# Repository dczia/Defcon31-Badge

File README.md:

# Defcon31-Badge
DCZia 2023 DC31 Badge - Electric Sampler

```
   ____  ___________   _          ________          __       _
   / __ \/ ____/__  /  (_)___ _   / ____/ /__  _____/ /______(_)____
  / / / / /      / /  / / __ `/  / __/ / / _ \/ ___/ __/ ___/ / ___/
 / /_/ / /___   / /__/ / /_/ /  / /___/ /  __/ /__/ /_/ /  / / /__
/_____/\____/  /____/_/\__,_/  /_____/_/\___/\___/\__/_/  /_/\___/

   _____                       __
  / ___/____ _____ ___  ____  / /__  _____
  \__ \/ __ `/ __ `__ \/ __ \/ / _ \/ ___/
 ___/ / /_/ / / / / / / /_/ / /  __/ /
/____/\__,_/_/ /_/ /_/ .___/_/\___/_/
                    /_/
```

## About
The DCZia Electric Sampler - A eurorack format drum machine, sampler, and step sequencer powered by
the Pi2040.

## Specs

RPI 2040 Microconroller
OLED Screen
3.5mm Audio Out Jack
3.5mm Midi In / Out (TRRS)
3.5mm Sync In / Out
MicroSD Card Slot
Eurorack Power Connector
Battery Power

## Build Guide

The badge comes with all surface mount components already assembled on the board. You will need to
solder on the keyswitches, audio jacks, screen, rotary encoders, and battery box.

First add the audio jacks. Install all the jacks and make sure they are flat and perpendicular with
the board. Next install the front board first aligning the jacks with the holes in the front board.
Then connect the bottom pin header to the front board. The header will be off by one, THIS IS OK for
the v1.1 board! Then carefully flip over the board and solder on the jacks.

Remove the front panel.

Then insert a keyswitch, or all keyswitches onto the board. Check that the metal pins are not bent,
and if so gently straignten them out with your fingers or a pair of tweezers. Carfully flip the
board over and solder on the keyswitches.

Next add the rotary encoders. Push them through the board, and you may need to gently fold in the
side stabilization pins if they do not line up correctly. Flip over the board and solder these in. 

Next with the board facing forward and on a flat surface, put the screen in. The legs of the screen
should not protrude through the back of the board past the holes, or only a tiny bit. You may need
to use something like a pencil or something to help the screen lay flat, standing off from the
board. Gently solder from the front to establish a mechanical connection to the board, then once the
screen is secure, flip over and solder the back. You must solder the back pads to endure a
connection from the screen to the microcrontroller. 

Finally flip the board over and gently attach the battery pack somewhere on the back with the
supplied double sticky tape. Then solder on the leads from the battery pack to the pads on the
bottom left side of the back of the board.

## User Manual

Currently the firmware is not complete, and the user interface may change.

The Select Knob will change between options on the screen, and push selects the currently
highlighted option.

The Volume knob will change the volume.

The PLAY button will play / pause any currently running program

There are a few modes on the v1 software.
A LED light mode.
A Sampler mode with a sequencer. You can load a wav file from the onboard flash, and then add a sequence and control the steps with the 8 key switches, and adjust per step volume.
A Sequencer mode which will play pre progarmed sequences. (Still under dev)
A Midi controller mode. You can adjust what notes / cc params are output via the python code in our repo.
A USB HID Device mode. The keys will output 0-9 and the device will emulate a keyboard.

## Notes

If you picked up a V1 board at Con, the board shipped with our testing firmware. Please flash the V1 firmware for more features.

Additional Features and changes will be coming soon!

## Updating the software / firmware

To update the software on the board you can do two things.

1. Use the fimware blob from our release section. To use this, unplug and turn off the module. Using something non conductivem press and hold the button on the RPI 2040 (The BootSelect Button) while powering on the unit via a micro usb cable. You should then see a mass storage drive appear on your computer. Drag the single uf2 file onto the drive. Then the unit should restart with the new firmware.

2. You can also plug the unit into your computer via the micro usb and drag the contents of the Production/Software folder onto the mass storage drive. The unit should reboot when complete. Sometimes if your computer transfers the files too slow this can cause issues with the RPI rebooting before all the software is complete.

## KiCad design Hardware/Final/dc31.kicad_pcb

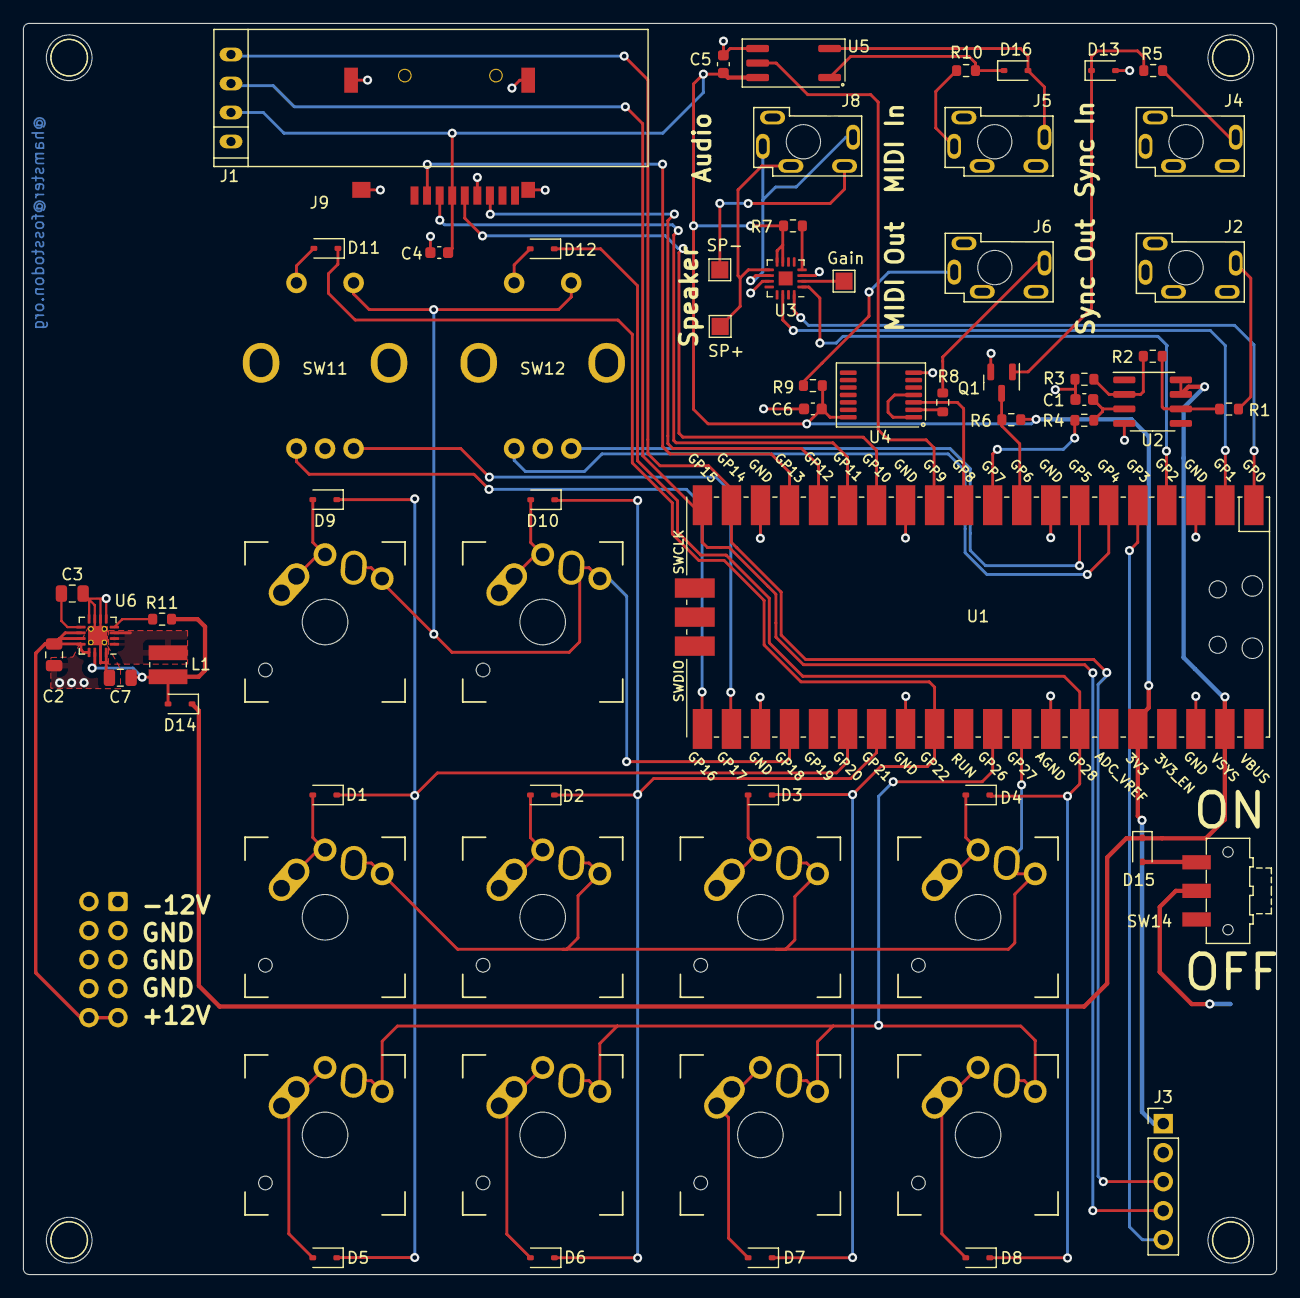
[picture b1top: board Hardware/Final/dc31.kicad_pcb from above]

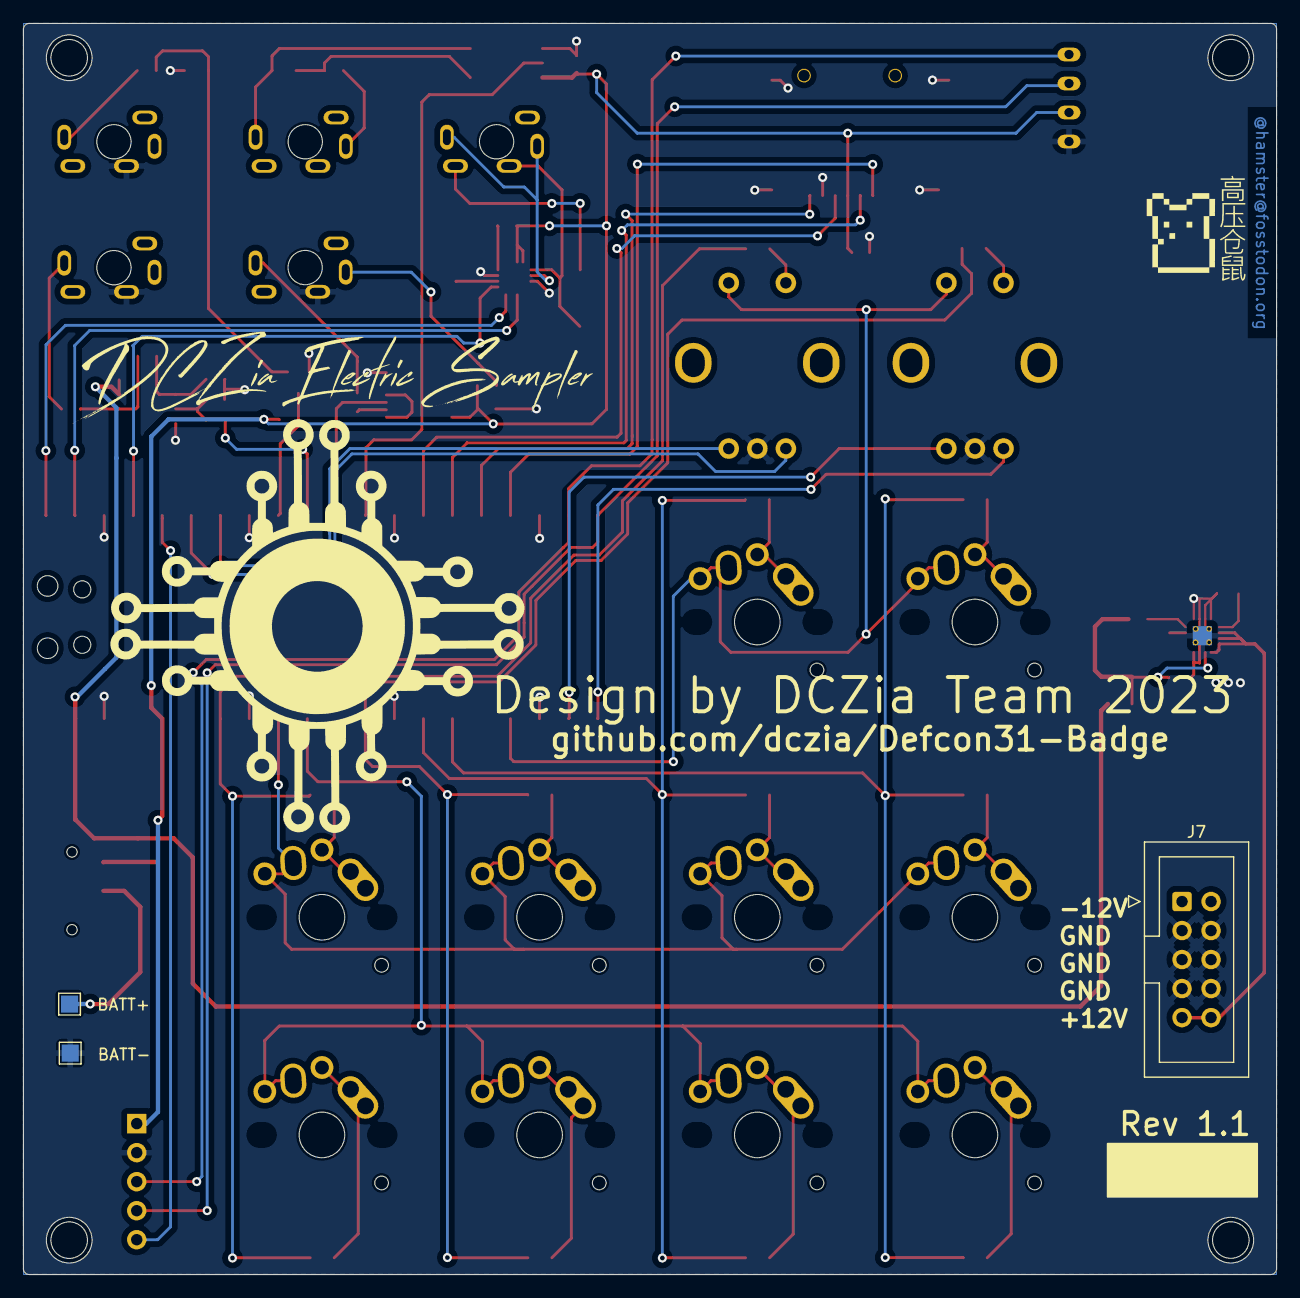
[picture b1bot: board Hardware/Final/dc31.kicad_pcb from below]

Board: 2 copper layers, 109.7 x 109.5 mm, 73 parts (3 on the bottom side), 65 nets.

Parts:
C1, C4, C5, C6: 0.1uF; C_0603_1608Metric
C2: 10uF; C_0805_2012Metric
C3: 3.3nF; C_0805_2012Metric
C7: 22uF; C_0805_2012Metric
D1, D2, D3, D4, D5, D6, D7, D8, D9, D10, D11, D12, D13, D16: D_Small_Filled; D_SOD-323
D14, D15: D_Schottky; D_SOD-323
HOLE1, HOLE2, HOLE3, HOLE4: MountingHole_1.6
J1: OLED
J2: SYNC OUT; STX-3790-5N
J3: FRONT; PinHeader_1x05_P2.54mm_Vertical
J4: SYNC IN; STX-3790-5N
J5: MIDI IN; STX-3790-5N
J6: MIDI OUT; STX-3790-5N
J7: Eurorack; IDC-Header_2x05_P2.54mm_Vertical
J8: HEADPHONE; STX-3790-5N
J9: Micro_SD_Card_SPI; MicroSD-Socket-Seeed-320090008
L1: 2.2uH; L_Wuerth_MAPI-3015
Q1: 3904; SOT-23
R1, R4: 1k; R_0603_1608Metric
R2: 220k; R_0603_1608Metric
R3, R5, R11: 100k; R_0603_1608Metric
R6: 10k; R_0603_1608Metric
R7: 1M; R_0603_1608Metric
R8: 10R; R_0603_1608Metric
R9: 33R; R_0603_1608Metric
R10: 220R; R_0603_1608Metric
SW1: Seq1; MX-Alps-Choc-1U
SW2: Seq2; MX-Alps-Choc-1U
SW3: Seq3; MX-Alps-Choc-1U
SW4: Seq4; MX-Alps-Choc-1U
SW5: Seq5; MX-Alps-Choc-1U
SW6: Seq6; MX-Alps-Choc-1U
SW7: Seq7; MX-Alps-Choc-1U
SW8: Seq8; MX-Alps-Choc-1U
SW9: PlayPause; MX-Alps-Choc-1U
SW10: Function; MX-Alps-Choc-1U
SW11: Function Select; RotaryEncoder
SW12: Volume; RotaryEncoder
SW14: SW_SPDT; SW_SPDT_CK-JS102011SAQN
TP1: Gain; TestPoint_Pad_1.5x1.5mm
TP2: BATT+; TestPoint_Pad_1.5x1.5mm
TP3: BATT-; TestPoint_Pad_1.5x1.5mm
TP4: SP-; TestPoint_Pad_1.5x1.5mm
TP5: SP+; TestPoint_Pad_1.5x1.5mm
U1: Pico; RPi_Pico_SMD
U2: OPA341UA; SOIC-8_3.9x4.9mm_P1.27mm
U3: MAX98357A/B; TQFN-16-1EP_3x3mm_P0.5mm_EP1.23x1.23mm
U4: 74HC04; TSSOP-14_4.4x5mm_P0.65mm
U5: TLP2361; SO-5_4.4x3.6mm_P1.27mm
U6: TPS62153; VQFN-16-1EP_3x3mm_P0.5mm_EP1.68x1.68mm_ThermalVias

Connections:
+3V3: C4.2, C5.1, C6.1, J1.2, J3.1, J9.4 (VDD), R6.2, R7.1, R9.2, U1.36 (3V3), U3.7 (Vdd), U3.8 (Vdd), U4.14 (VCC), U5.6 (VCC)
+5V: C7.1, D14.2 (A), L1.2, R11.2, U6.14 (VOS)
+12V: C2.1, J7.9, J7.10, U6.10 (AVIN), U6.11 (PVIN), U6.12 (PVIN), U6.13 (EN)
C0: SW1.1, SW2.1, SW3.1, SW4.1, U1.32 (GPIO27_ADC1)
C1: SW5.1, SW6.1, SW7.1, SW8.1, U1.31 (GPIO26_ADC0)
C2: SW9.1, SW10.1, SW11.S2, SW12.S2, U1.24 (GPIO18)
ENC1_A: SW11.A, U1.21 (GPIO16)
ENC1_B: SW11.B, U1.22 (GPIO17)
ENC1_SW: D11.2 (A), SW11.S1
ENC2_A: SW12.A, U1.6 (GPIO4)
ENC2_B: SW12.B, U1.7 (GPIO5)
ENC2_SW: D12.2 (A), SW12.S1
GND: C1.2, C2.2, C3.2, C4.1, C5.2, C6.2, C7.2, D13.2 (A), J1.1, J2.5, J3.2, J4.5, J6.5, J7.3, J7.4, J7.5, J7.6, J7.7, J7.8, J9.6 (VSS), J9.10 (SHIELD), Q1.2 (E), R3.1, SW11.C, SW12.C, TP3.1, U1.3 (GND), U1.8 (GND), U1.13 (GND), U1.18 (GND), U1.23 (GND), U1.28 (GND), U1.33 (AGND), U1.38 (GND), U2.4 (V-), U3.3 (GND), U3.11 (GND), U4.7 (GND), U5.4 (GND), U6.5 (FB), U6.6 (AGND), U6.7 (FSW), U6.8 (DEF), U6.15 (PGND), U6.16 (PGND), U6.17 (EP)
I2S_BCLK: U1.1 (GPIO0), U3.16 (BCLK)
I2S_DIN: U1.4 (GPIO2), U3.1 (DIN)
I2S_LRCLK: U1.2 (GPIO1), U3.14 (LRCLK)
MIDI_IN: U1.12 (GPIO9), U5.5
MIDI_OUT: U1.11 (GPIO8), U4.3
unnamed: D1.2 (A), SW1.2
unnamed: D2.2 (A), SW2.2
unnamed: D3.2 (A), SW3.2
unnamed: D4.2 (A), SW4.2
unnamed: D5.2 (A), SW5.2
unnamed: D6.2 (A), SW6.2
unnamed: D7.2 (A), SW7.2
unnamed: D8.2 (A), SW8.2
unnamed: D9.2 (A), SW9.2
unnamed: D10.2 (A), SW10.2
unnamed: D13.1 (K), Q1.1 (B), R5.2
unnamed: D15.2 (A), SW14.3 (C)
unnamed: D16.2 (A), J5.4, U5.3
unnamed: D16.1 (K), R10.2, U5.1
unnamed: J2.4, R1.1
unnamed: J4.4, R5.1
unnamed: J5.1, R10.1
unnamed: J6.1, R9.1
unnamed: J6.4, R8.1
unnamed: J8.3, TP5.1
unnamed: L1.1, U6.1 (SW), U6.2 (SW), U6.3 (SW)
unnamed: R1.2, R2.1, U2.6
unnamed: R8.2, U4.2
unnamed: SW14.2 (B), TP2.1
unnamed: C1.1, R4.1, U2.3 (+)
unnamed: R2.2, R3.2, U2.2 (-)
unnamed: TP1.1, U3.2 (GAIN_SLOT)
unnamed: J8.1, J8.4, U3.10 (OUTN)
unnamed: J8.5, TP4.1, U3.9 (OUTP)
unnamed: R7.2, U3.4 (~SD_MODE)
unnamed: U4.1, U4.4
unnamed: R11.1, U6.4 (PG)
unnamed: C3.1, U6.9 (SS/TR)
R0: D1.1 (K), D5.1 (K), D9.1 (K), U1.26 (GPIO20)
R1: D2.1 (K), D6.1 (K), D10.1 (K), U1.27 (GPIO21)
R2: D3.1 (K), D7.1 (K), D11.1 (K), U1.29 (GPIO22)
R3: D4.1 (K), D8.1 (K), D12.1 (K), U1.34 (GPIO28_ADC2)
RGB: J3.5, U1.5 (GPIO3)
SCL: J1.3, J3.4, U1.20 (GPIO15)
SDA: J1.4, J3.3, U1.19 (GPIO14)
SD_CS: J9.2 (/CS), U1.17 (GPIO13)
SD_MISO: J9.7 (DO), U1.16 (GPIO12)
SD_MOSI: J9.3 (DI), U1.15 (GPIO11)
SD_SCK: J9.5 (CLK), U1.14 (GPIO10)
SYNC_IN: Q1.3 (C), R6.1, U1.9 (GPIO6)
SYNC_OUT: R4.2, U1.10 (GPIO7)
VCC: D14.1 (K), D15.1 (K), U1.39 (VSYS), U2.7 (V+), U2.8 (~SHDN)

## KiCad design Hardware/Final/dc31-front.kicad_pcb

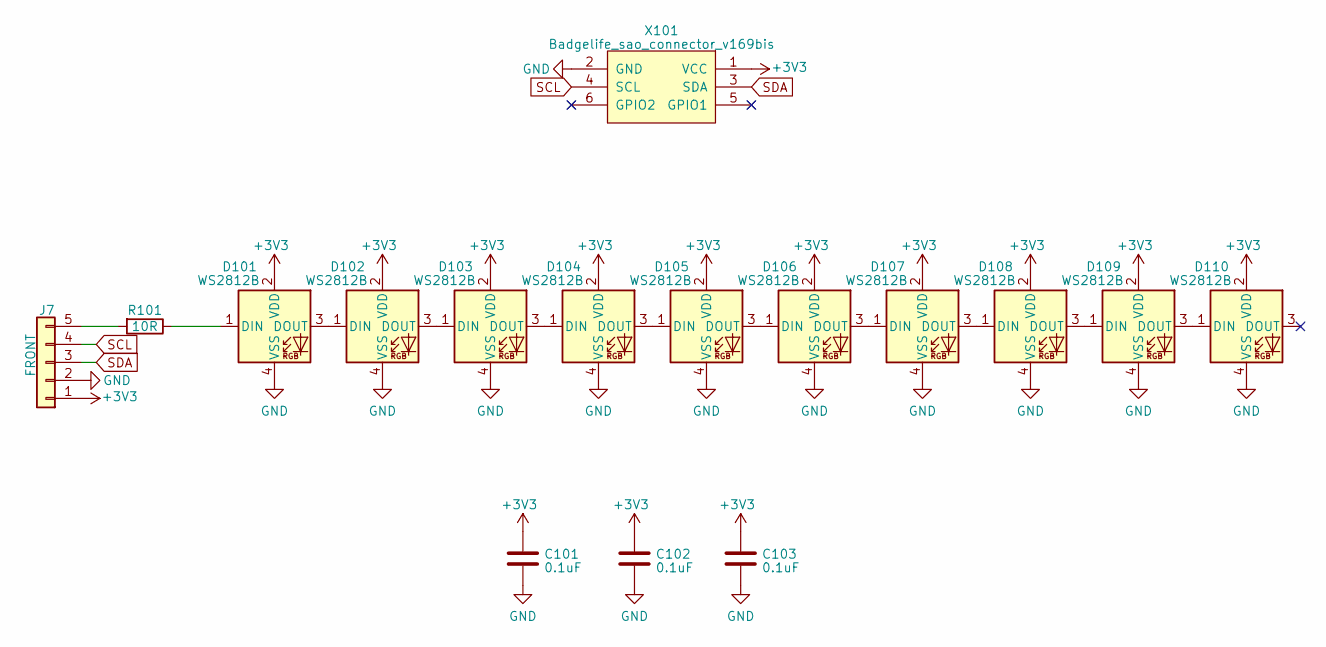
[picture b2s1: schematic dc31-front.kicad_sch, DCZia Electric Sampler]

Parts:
C101, C102, C103: 0.1uF; C_0603_1608Metric
D101, D102, D103, D104, D105, D106, D107, D108, D109, D110: WS2812B; LED_SK6812_4020_
J7: FRONT; PinSocket_1x05_P2.54mm_Vertical_SMD_Pin1Left
R101: 10R; R_0603_1608Metric
X101: Badgelife_sao_connector_v169bis; Badgelife-Shitty-v1.69bis

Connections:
+3V3: C101.1, C102.1, C103.1, D101.2 (VDD), D102.2 (VDD), D103.2 (VDD), D104.2 (VDD), D105.2 (VDD), D106.2 (VDD), D107.2 (VDD), D108.2 (VDD), D109.2 (VDD), D110.2 (VDD), X101.1 (VCC); also elsewhere on the board
GND: C101.2, C102.2, C103.2, D101.4 (VSS), D102.4 (VSS), D103.4 (VSS), D104.4 (VSS), D105.4 (VSS), D106.4 (VSS), D107.4 (VSS), D108.4 (VSS), D109.4 (VSS), D110.4 (VSS), X101.2 (GND); also elsewhere on the board
unnamed: D101.1 (DIN), R101.1
unnamed: D101.3 (DOUT), D102.1 (DIN)
unnamed: D102.3 (DOUT), D103.1 (DIN)
unnamed: D103.3 (DOUT), D104.1 (DIN)
unnamed: D104.3 (DOUT), D105.1 (DIN)
unnamed: D105.3 (DOUT), D106.1 (DIN)
unnamed: D106.3 (DOUT), D107.1 (DIN)
unnamed: D107.3 (DOUT), D108.1 (DIN)
unnamed: D108.3 (DOUT), D109.1 (DIN)
unnamed: D109.3 (DOUT), D110.1 (DIN)
unnamed 12: R101.2; also elsewhere on the board
SCL: X101.4 (SCL); also elsewhere on the board
SDA: X101.3 (SDA); also elsewhere on the board

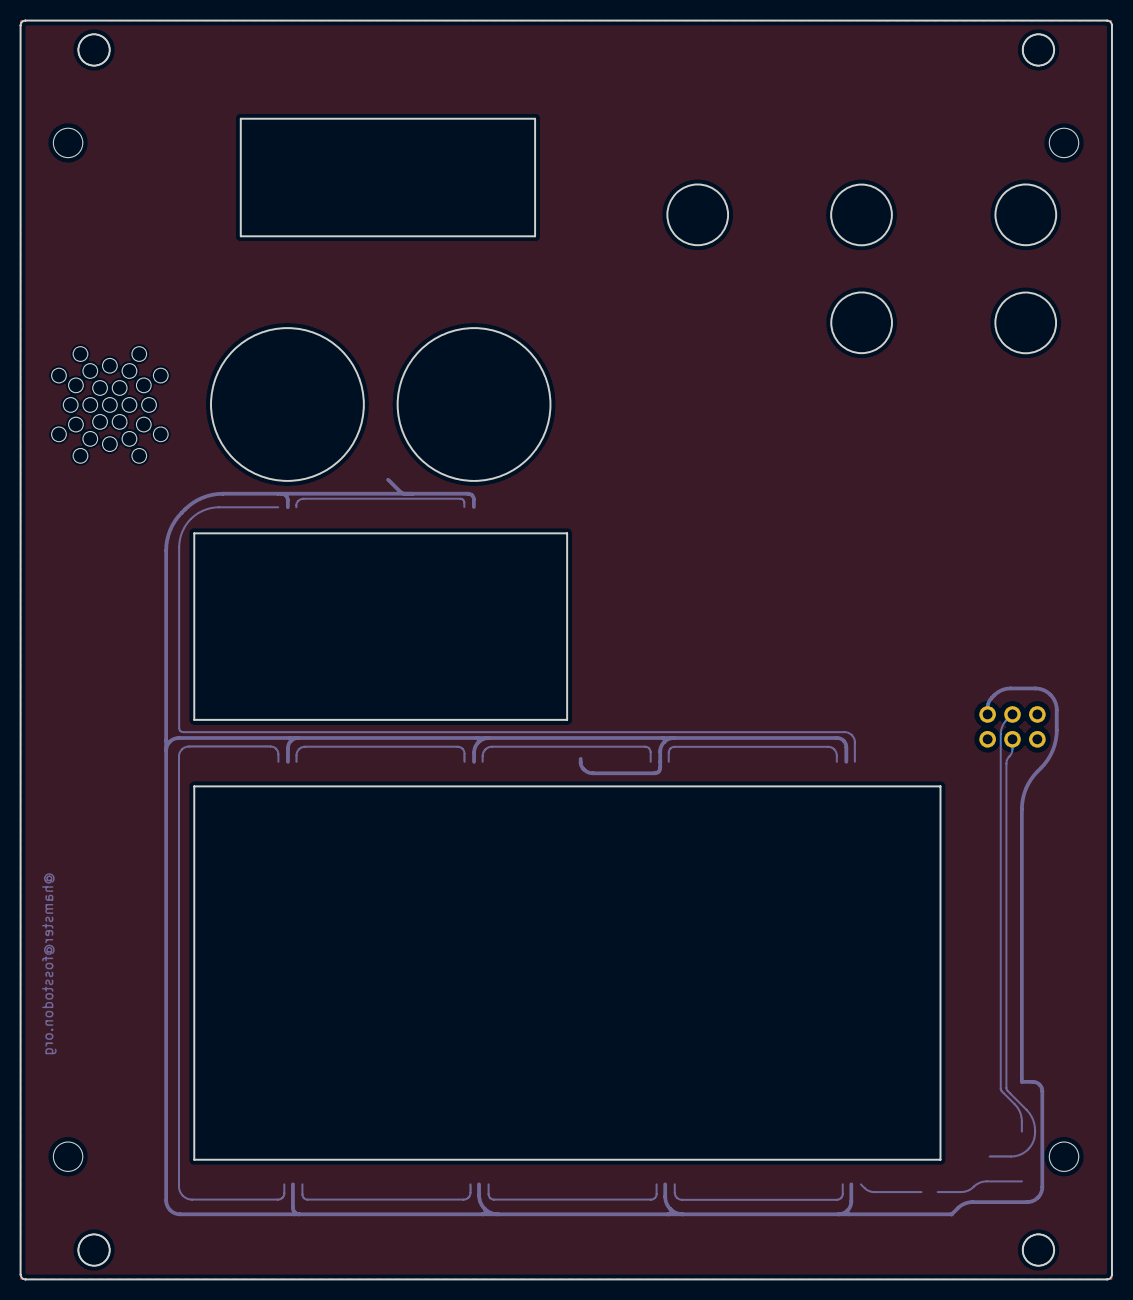
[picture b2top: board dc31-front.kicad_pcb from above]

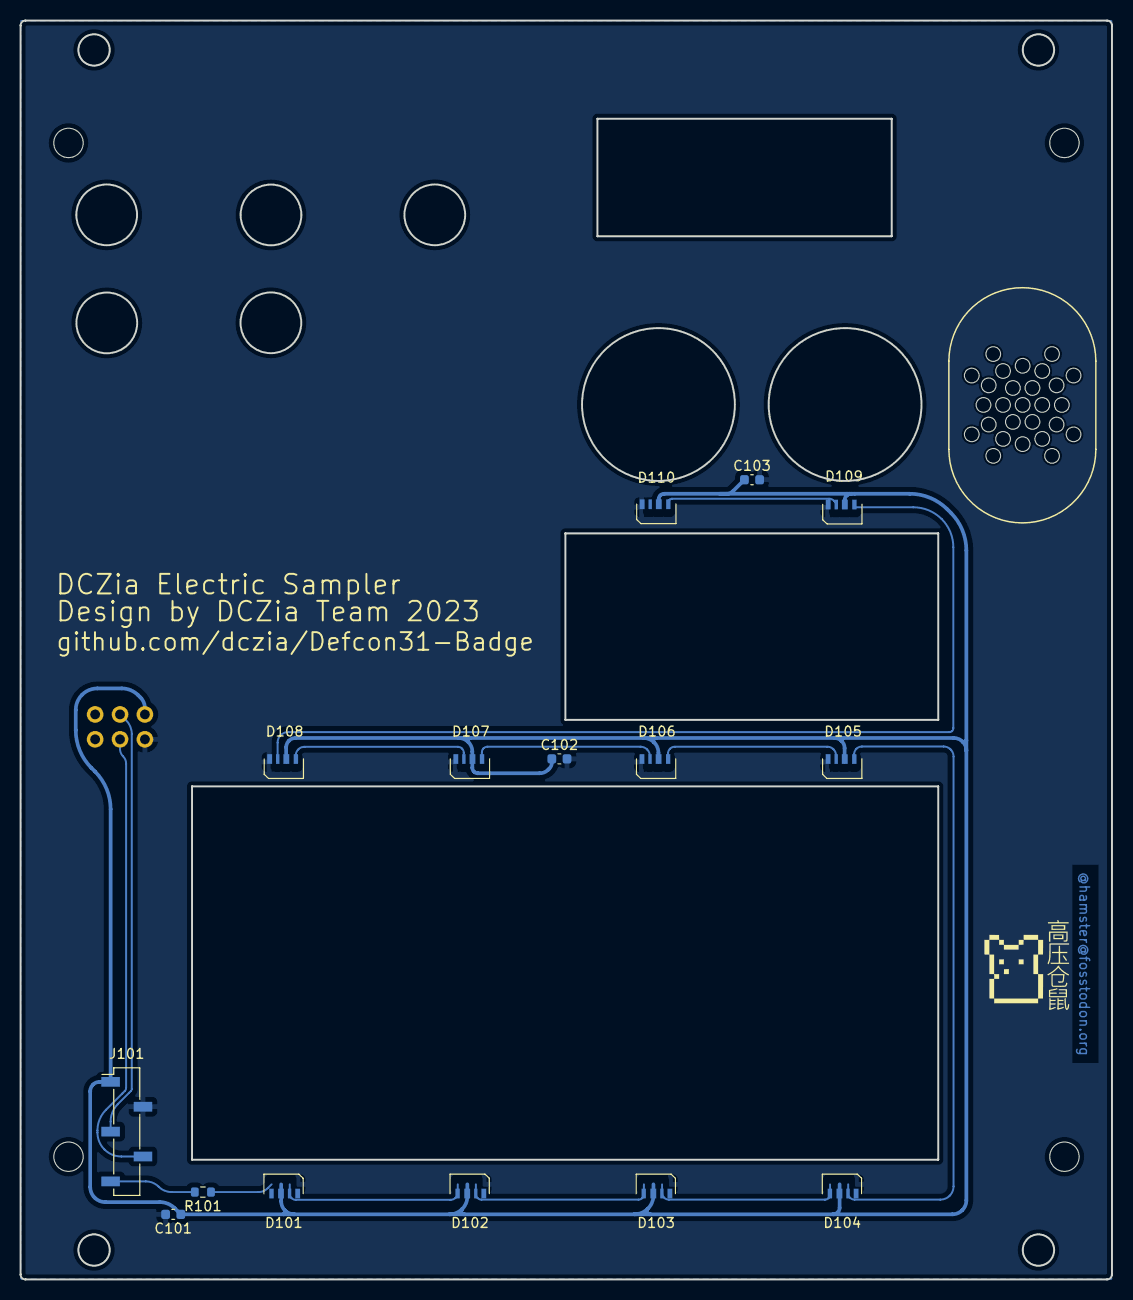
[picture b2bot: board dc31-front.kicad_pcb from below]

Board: 2 copper layers, 111.4 x 128.5 mm, 20 parts (15 on the bottom side), 15 nets.

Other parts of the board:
HOLE1, HOLE2, HOLE3, HOLE4: MountingHole_1.6
J101: FRONT; PinSocket_1x05_P2.54mm_Vertical_SMD_Pin1Left

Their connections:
+3V3: J101.1; also elsewhere on the board
GND: J101.2; also elsewhere on the board
unnamed 12: J101.5; also elsewhere on the board
SCL: J101.4; also elsewhere on the board
SDA: J101.3; also elsewhere on the board

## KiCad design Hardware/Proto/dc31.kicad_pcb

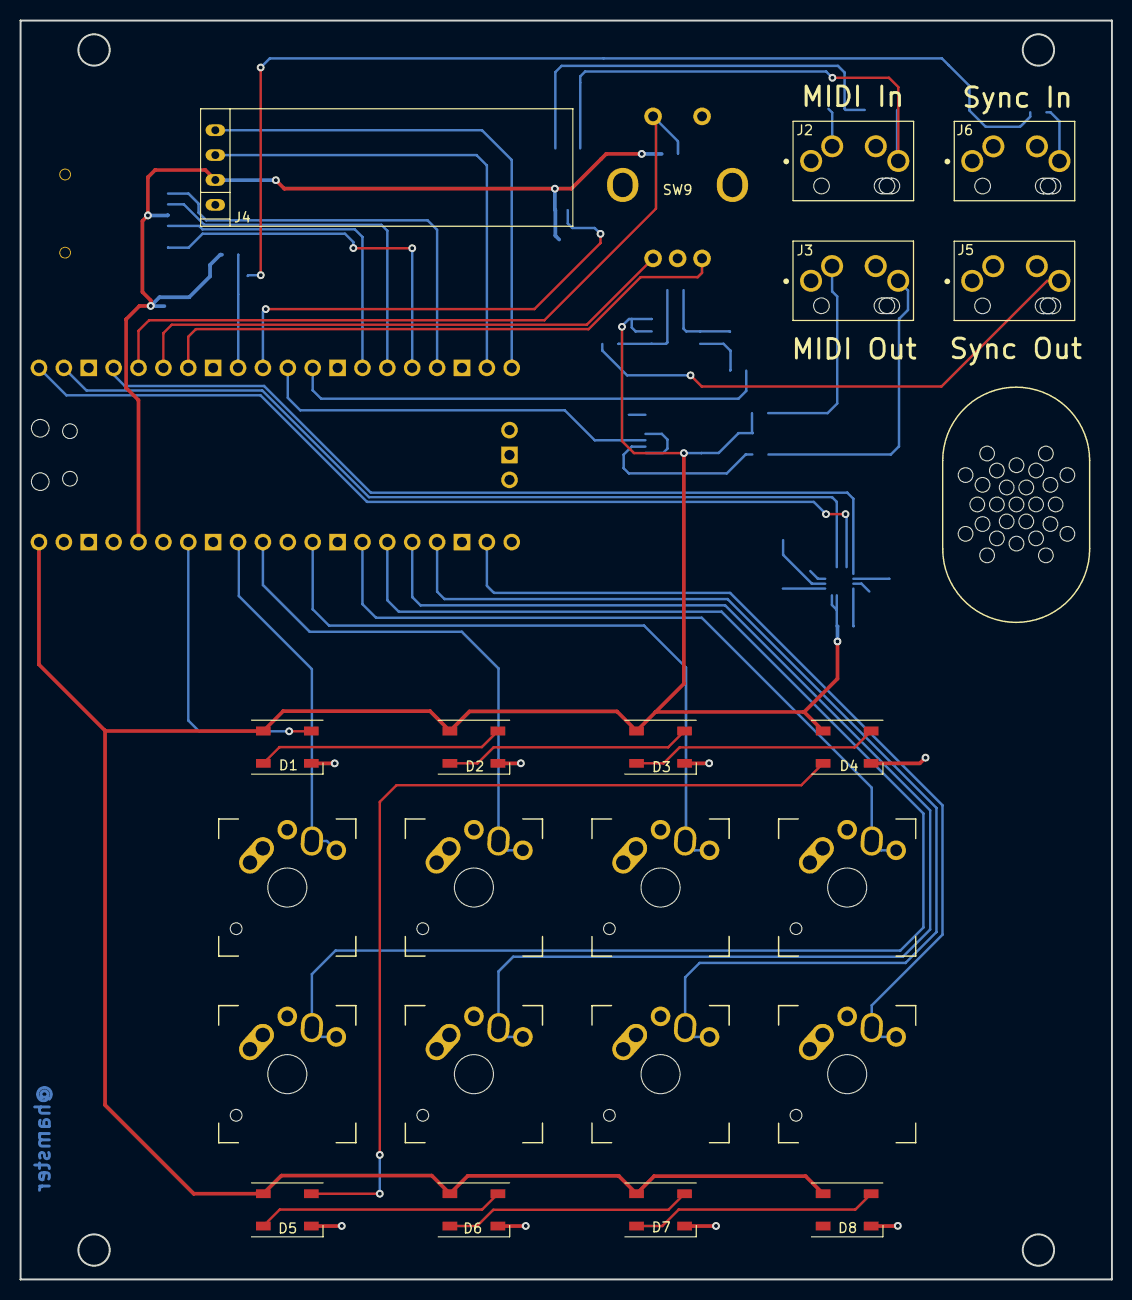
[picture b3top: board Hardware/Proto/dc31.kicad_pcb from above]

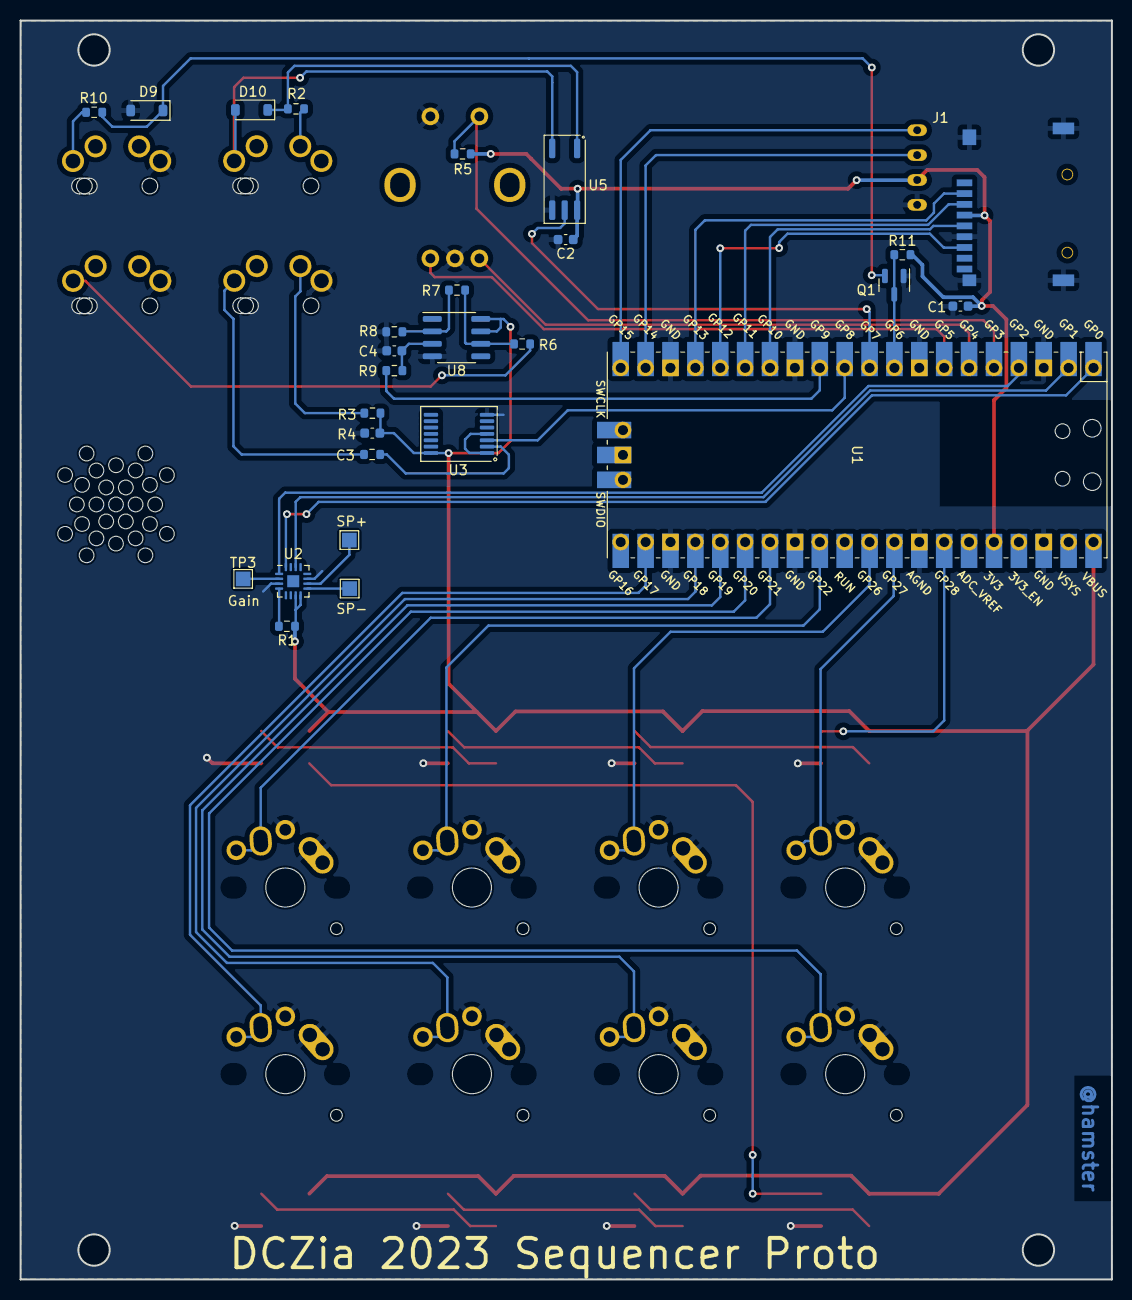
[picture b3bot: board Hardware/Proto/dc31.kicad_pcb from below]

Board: 2 copper layers, 111.4 x 128.5 mm, 49 parts (27 on the bottom side), 52 nets.

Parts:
C1, C2, C3, C4: 0.1uF; C_0603_1608Metric
D1, D2, D3, D4, D5, D6, D7, D8: WS2812B; LED_WS2812B_PLCC4_5.0x5.0mm_P3.2mm
D9, D10: D_Small_Filled; D_SOD-123
J1: Micro_SD_Card_SPI; MicroSD-Socket-Seeed-320090008
J2: MIDI IN; MOLEX_47257-0001
J3: MIDI OUT; MOLEX_47257-0001
J4: OLED
J5: SYNC OUT; MOLEX_47257-0001
J6: SYNC IN; MOLEX_47257-0001
Q1: 3904; SOT-23
R1: 1M; R_0603_1608Metric
R2, R3, R4: 220R; R_0603_1608Metric
R5, R11: 10k; R_0603_1608Metric
R6, R9: 1k; R_0603_1608Metric
R7: 220k; R_0603_1608Metric
R8, R10: 100k; R_0603_1608Metric
SW1, SW2, SW3, SW4, SW5, SW6, SW7, SW8: SW_Push; MX-Alps-Choc-1U
SW9: Rotary; RotaryEncoder
TP1: SP+; TestPoint_Pad_1.5x1.5mm
TP2: SP-; TestPoint_Pad_1.5x1.5mm
TP3: Gain; TestPoint_Pad_1.5x1.5mm
U1: Pico; RPi_Pico_SMD_TH
U2: MAX98357A/B; TQFN-16-1EP_3x3mm_P0.5mm_EP1.23x1.23mm
U3: 74HC04; TSSOP-14_4.4x5mm_P0.65mm
U5: TLP2361; SO-5_4.4x3.6mm_P1.27mm
U8: OPA341UA; SOIC-8_3.9x4.9mm_P1.27mm

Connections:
+3V3: C1.2, C2.1, J1.4 (VDD), J4.2, R5.1, R11.2, U1.36 (3V3), U5.6 (VCC)
ENC1_A: SW9.A, U1.6 (GPIO4)
ENC1_B: SW9.B, U1.7 (GPIO5)
ENC1_SW: R5.2, SW9.S1, U1.5 (GPIO3)
GND: C1.1, C2.2, C3.2, C4.2, D1.3 (VSS), D2.3 (VSS), D3.3 (VSS), D4.3 (VSS), D5.3 (VSS), D6.3 (VSS), D7.3 (VSS), D8.3 (VSS), D9.2 (A), J1.6 (VSS), J1.10 (SHIELD), J3.1, J4.1, J5.1, J6.1, Q1.1 (E), R8.1, SW1.2, SW2.2, SW3.2, SW4.2, SW5.2, SW6.2, SW7.2, SW8.2, SW9.C, SW9.S2, U1.3 (GND), U1.8 (GND), U1.13 (GND), U1.18 (GND), U1.23 (GND), U1.28 (GND), U1.33 (AGND), U1.38 (GND), U2.3 (GND), U2.11 (GND), U3.7 (GND), U5.4 (GND), U8.4 (V-)
I2S_BCLK: U1.1 (GPIO0), U2.16 (BCLK)
I2S_DIN: U1.4 (GPIO2), U2.1 (DIN)
I2S_LRCLK: U1.2 (GPIO1), U2.14 (LRCLK)
MIDI_IN: U1.10 (GPIO7), U5.5
MIDI_OUT: U1.11 (GPIO8), U3.3
unnamed: D1.2 (DOUT), D2.4 (DIN)
unnamed: D2.2 (DOUT), D3.4 (DIN)
unnamed: D3.2 (DOUT), D4.4 (DIN)
unnamed: D4.2 (DOUT), D5.4 (DIN)
unnamed: D5.2 (DOUT), D6.4 (DIN)
unnamed: D6.2 (DOUT), D7.4 (DIN)
unnamed: D7.2 (DOUT), D8.4 (DIN)
unnamed: D9.1 (K), Q1.2 (B), R10.2
unnamed: D10.2 (A), J2.2, U5.3
unnamed: D10.1 (K), R2.2, U5.1
unnamed: J2.3, R2.1
unnamed: J3.2, R4.1
unnamed: J3.3, R3.1
unnamed: J5.2, R6.1
unnamed: J6.2, R10.1
unnamed: R4.2, U3.2
unnamed: R6.2, R7.1, U8.6
unnamed: TP3.1, U2.2 (GAIN_SLOT)
unnamed: TP2.1, U2.10 (OUTN)
unnamed: TP1.1, U2.9 (OUTP)
unnamed: R1.2, U2.4 (~SD_MODE)
unnamed: U3.1, U3.4
unnamed: C4.1, R9.1, U8.3 (+)
unnamed: R7.2, R8.2, U8.2 (-)
RGB_IN: D1.4 (DIN), U1.34 (GPIO28_ADC2)
SCL: J4.3, U1.19 (GPIO14)
SDA: J4.4, U1.20 (GPIO15)
SD_CS: J1.2 (/CS), U1.17 (GPIO13)
SD_MISO: J1.7 (DO), U1.16 (GPIO12)
SD_MOSI: J1.3 (DI), U1.15 (GPIO11)
SD_SCK: J1.5 (CLK), U1.14 (GPIO10)
SW1: SW1.1, U1.32 (GPIO27_ADC1)
SW2: SW2.1, U1.31 (GPIO26_ADC0)
SW3: SW3.1, U1.29 (GPIO22)
SW4: SW4.1, U1.27 (GPIO21)
SW5: SW5.1, U1.26 (GPIO20)
SW6: SW6.1, U1.25 (GPIO19)
SW7: SW7.1, U1.24 (GPIO18)
SW8: SW8.1, U1.22 (GPIO17)
SYNC_IN: Q1.3 (C), R11.1, U1.9 (GPIO6)
SYNC_OUT: R9.2, U1.12 (GPIO9)
VBUS: C3.1, D1.1 (VDD), D2.1 (VDD), D3.1 (VDD), D4.1 (VDD), D5.1 (VDD), D6.1 (VDD), D7.1 (VDD), D8.1 (VDD), R1.1, R3.2, U1.40 (VBUS), U2.7 (Vdd), U2.8 (Vdd), U3.14 (VCC), U8.7 (V+), U8.8 (~SHDN)

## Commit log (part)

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2023-07-09 Adding proto files to repo. This is As-Built proto.
2023-07-11 Adding test firmware Adding some 3d parts Some updates to the schematic as we prepare for final
2023-07-11 Adding some jank tests for midi, volume, controls, and a sequencer
2023-07-11 Adding adafruit_midi lib to main
2023-07-11 Update schematic and flesh out BOM with parts
2023-07-12 Update README.md
    Updated initial Readme. Need to change todo items into issues / tasks
2023-07-14 Schematic is pretty much complete. Back board is 90% routed.
2023-07-15 State machine framework built. Basic I/O mostly implemented, and skeletons for most modes in place.
2023-07-15 Update README.md
    Fixing derp formatting in readme
2023-07-15 Add start up splash text. Add Main Menu
2023-07-15 Removed some print debugging
2023-07-15 Almost final, still need some artwork
2023-07-15 Menu Updates
2023-07-16 Update to add a Documentation task to the Readme.
    Add a documentation task to the Readme.
2023-07-16 Adding SAO port to front panel Adding hamster art to boards A few more small tweaks before final export
2023-07-19 Final files as submitted to fab
2023-07-22 Stickers part 1
2023-07-22 Change menu design
2023-07-22 Add files via upload
    dczia_badge_github_qr image
2023-07-22 add dczia webpage qr code
    add dczia webpage qr code
2023-07-22 Add menu selection highlighting
2023-07-22 More menu tweaks
2023-07-22 Code Clean Up
2023-07-23 Generated 1.1 rev to switch to KYCON 3.5mm jacks due to parts issues with the Molex
2023-07-23 Update BOM
2023-07-23 Add USB-HID example
2023-07-23 Add CI
2023-07-23 Run "black" python formatter on both files for cleanup
2023-07-23 Fix all the linting errors
2023-07-23 Fixed typo
2023-07-23 Reformatter
2023-07-23 Activate Menu
2023-07-23 Beardbyte changes (#22)
    * Beardbyte menu adventures
    ---------
2023-07-26 Refactor menu to use dictionary array
2023-07-26 Refactor menu to use dictionary array (#23)
2023-07-26 First cut at multi-track sampler, added new wav files
    Added rough cut of sequencer programming interface, some sequencer related led code
    Matching formatting
2023-07-26 First cut at multi-track sampler, added new wav files (#25)
    Added rough cut of sequencer programming interface, some sequencer related led code
    Matching formatting
2023-07-26 Random refactoring
2023-07-26 Pretty lights
2023-07-26 Dummy Sampler With Pretty Lights
2023-07-26 Add USB HID mode
2023-07-26 Remove function calls at base level
2023-07-26 Add USB HID mode (#26)
2023-07-26 Remove function calls at base level (#28)
2023-07-26 Pretty lights (#27)
2023-07-26 Adjust lighting in HID mode
2023-07-26 Adjust lighting in HID mode (#29)
2023-07-26 Adjust MIDIState to be state-machine-y
2023-07-26 Adjust MIDIState to be state-machine-y (#30)
2023-07-27 First cut at multi-track sampler, added new wav files (#31)
    Added rough cut of sequencer programming interface, some sequencer related led code
    Matching formatting
2023-07-28 Fix USB-HID bug
    When the badge is not plugged into a computer it doesn't start correctly
    because there is not USB host to create a virtual keyboard for
2023-07-28 MOAR PRETTY COLORS
2023-07-28 MOAR PRETTY COLORS (#33)
2023-07-28 Fix USB-HID bug (#32)
    When the badge is not plugged into a computer it doesn't start correctly
    because there is not USB host to create a virtual keyboard for
2023-07-28 USB MIDI out implemented
2023-07-28 USB MIDI out implemented (#34)
2023-07-28 Make startup flashier
2023-07-28 Make startup flashier (#35)
2023-07-28 Make the linter pass
2023-07-28 Make the linter pass (#37)
2023-07-28 Improving sampler functionality
2023-07-28 Improvements to menu states and flow
2023-07-28 Add try/except for when an SD card is not loaded
2023-07-28 Sampler improvements (#38)
    * Improving sampler functionality
    * Improvements to menu states and flow
    ---------
2023-07-28 Sd exception (#39)
    * Improving sampler functionality
    * Improvements to menu states and flow
    * Add try/except for when an SD card is not loaded
    ---------
2023-07-29 Add scrolling main menu
2023-07-30 Add scrolling main menu (#40)
2023-07-30 Move things into library files
    Move audio init into setup.py
    Move midi functions into midi.py
    Move menu functions into menu.py
    Move state to state.py
    Move FlashyState to flashy.py
    Refactor menuing to reduce use of global state
2023-08-01 Code for function testing the final badge.
    Written as a best guess, but no hardware to test on so modification may be needed.
2023-08-02 Cleanup and menu adjustments (no globals)
2023-08-02 Cleanup and menu adjustments (no globals) (#42)
2023-08-02 HID nitpick fixes
    - Handle more than one key event per update
    - Only call neopixels.show() once per update
    - Make keys number pad 1 through 8
2023-08-02 Updated some 3D models Updated BOM sheet Added bodge instructions Added some documentation
2023-08-03 Various hardware changes (#44)
    Updated some 3D models
    Updated BOM sheet
    Added bodge instructions
    Added some documentation
2023-08-03 HID nitpick fixes (#43)
    - Handle more than one key event per update
    - Only call neopixels.show() once per update
    - Make keys number pad 1 through 8
2023-08-03 Homogenize USB-MIDI based on USB-HID
2023-08-03 Update Sampler and Flashy to scrolling menus
2023-08-03 Format with black
2023-08-03 Update Sampler and Flashy to scrolling menus (#47)
    * Update Sampler and Flashy to scrolling menus
    * Format with black
2023-08-03 Remove unneeded colors calls
2023-08-03 Homogenize USB-MIDI based on USB-HID (#45)
2023-08-03 Remove unneeded colors calls (#46)
2023-08-03 Persist Flashy Mode
    - Move flashy selector to a function to be cleaner
    - Move flashy animation to machine to it is accessible from other states
2023-08-03 Persist Flashy Mode (#48)
    - Move flashy selector to a function to be cleaner
    - Move flashy animation to machine to it is accessible from other states
2023-08-03 Press encoder to skip intro
2023-08-03 Press encoder to skip intro (#49)
2023-08-04 Start creating production code
2023-08-04 Audio and keys tests confirmed working on prod hardware
2023-08-04 Start creating production code (#50)
2023-08-04 Add Midi Controller State
2023-08-04 Add USB-HID State
2023-08-05 Add FlashyState
2023-08-05 Add USB-HID State (#51)
2023-08-05 Add Midi Controller State (#52)
2023-08-05 Add FlashyState (#53)
2023-08-05 Add MenuState
2023-08-05 Fix MIDI error
    If a key is released when entering midi mode, an error occurs
2023-08-05 Add MenuState (#54)
2023-08-05 Fix MIDI error (#55)
    If a key is released when entering midi mode, an error occurs
2023-08-05 Initial framework for production sequencer/sampler states
2023-08-05 Initial framework for production sequencer/sampler states (#56)
2023-08-05 Add better select wav and sequence
2023-08-05 Add better select wav and sequence (#57)
2023-08-05 Add reindexer for neopixels
2023-08-06 Add reindexer for neopixels (#58)
2023-08-09 Sampler bugfixes and slight menu improvements
    Correction in neopixel mapping
    Added sampled (kick too low for speaker, but works on headphones)
    Changed default MIDI channel to 1
2023-08-09 Fixing LED indexing in MIDI controller and HID Controller Improving menu flow in sampler
2023-08-09 Add remove sequence function in SamplerMenuState Supressed print statement in menu function
2023-08-09 Sampler bugfixes and slight menu improvements (definitely not panic coding) (#61)
    Sampler bugfixes and slight menu improvements
    Correction in neopixel mapping
    Added sampled (kick too low for speaker, but works on headphones)
    Changed default MIDI channel to 1
2023-08-09 Neopixel and menu fixes (#62)
    * Sampler bugfixes and slight menu improvements
    Correction in neopixel mapping
    Added sampled (kick too low for speaker, but works on headphones)
    Changed default MIDI channel to 1
    * Fixing LED indexing in MIDI controller and HID Controller
    Improving menu flow in sampler
2023-08-09 Sequence remove menu (#63)
    * Sampler bugfixes and slight menu improvements
    Correction in neopixel mapping
    Added sampled (kick too low for speaker, but works on headphones)
    Changed default MIDI channel to 1
    * Fixing LED indexing in MIDI controller and HID Controller
    Improving menu flow in sampler
2023-08-11 Sequence remove menu (#63)
    * Sampler bugfixes and slight menu improvements
    Correction in neopixel mapping
    Added sampled (kick too low for speaker, but works on headphones)
    Changed default MIDI channel to 1
    * Fixing LED indexing in MIDI controller and HID Controller
    Improving menu flow in sampler
2023-08-11 Added 909 Samples
    909 Samples from my RD-9 Drum machine. Processed in live
2023-08-11 Lithobob manual samples (#65)
    * Added 909 Samples
    909 Samples from my RD-9 Drum machine. Processed in live
    * Update README.md
    * Updated Readme
2023-08-11 Creating uf2 to make flashing easier
2023-08-11 Creating uf2 to make flashing easier (#66)
2023-08-18 Added more user documentation for V1
2023-08-18 Added more user documentation for V1 (#67)
2023-08-22 Adding scale selection and octave selection to MIDI controller
2023-08-25 Adding scale selection and octave selection to MIDI controller (#68)
2023-09-22 Bugfix for Resolume functionality
2023-09-22 Bugfix for Resolume functionality (#70)
2025-07-12 Update for circuitpython 9, added reactive eye candy on trigger for the sync input, improved the MIDI input
